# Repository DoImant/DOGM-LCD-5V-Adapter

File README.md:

# 5V Adapter for the DOGMxxxxA Carrier Board.

This board is an adapter with which the 3.3V LCD-DOGMxxxx-A adapter board can also be operated with 5V (e.g. Arduino Nano/Uno).
Because the data flow is only unidirectional to the display, a 74LVC245A octal bus transceiver IC could be used as a level converter.

## Pictures
DOGM 5V to 3.3V Adapter. Front and back side.

Adapter board with LCD display on a breadboard.

Dogm LCD powerconsumption without backlight

Dogm LCD powerconsumtion with 25% backlight

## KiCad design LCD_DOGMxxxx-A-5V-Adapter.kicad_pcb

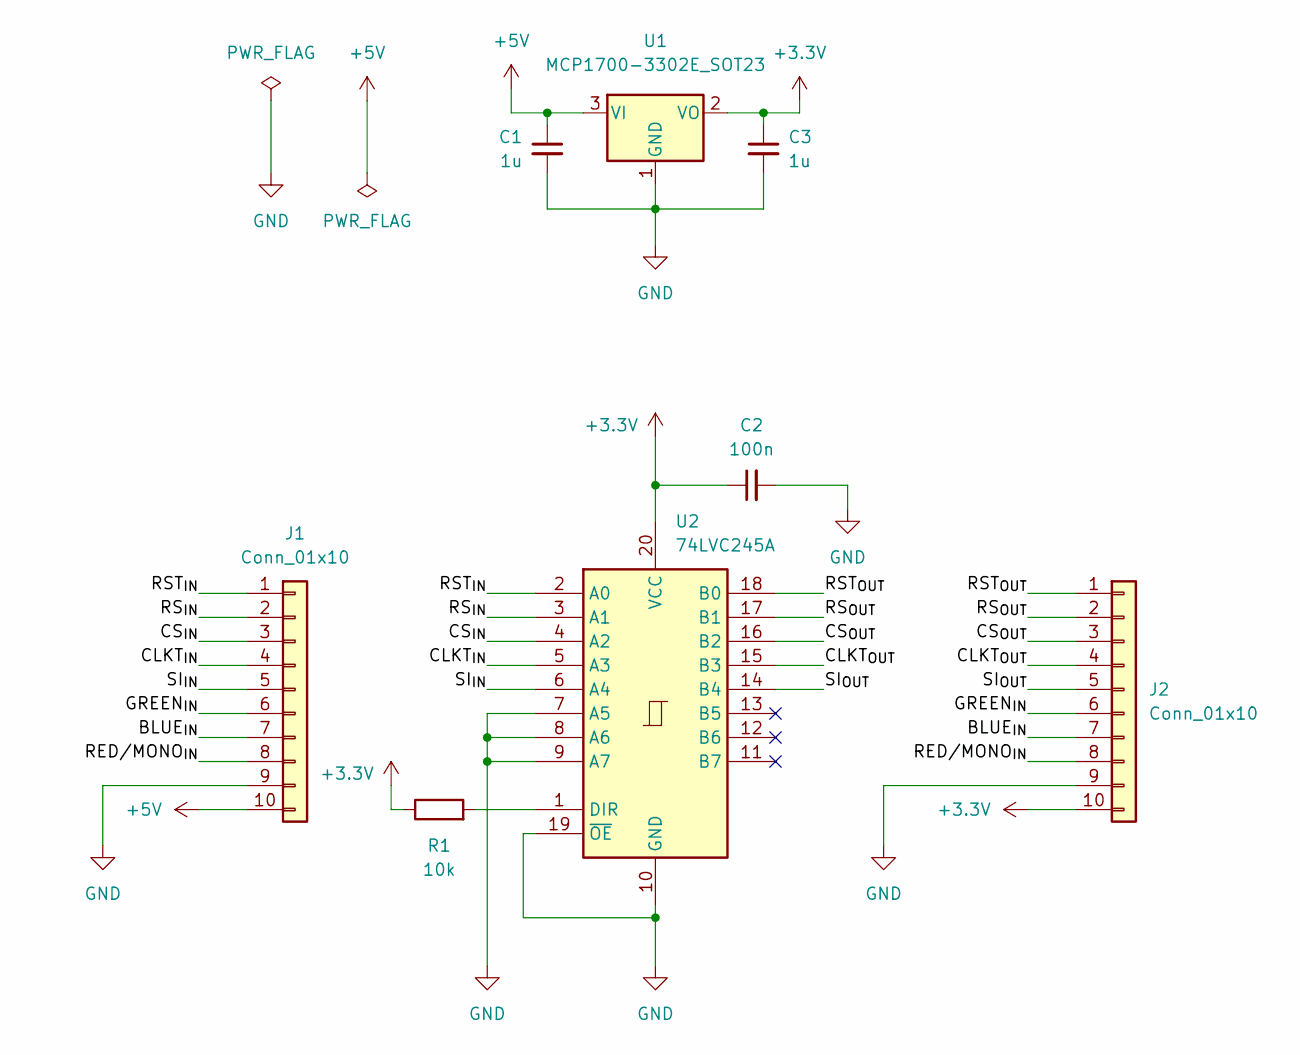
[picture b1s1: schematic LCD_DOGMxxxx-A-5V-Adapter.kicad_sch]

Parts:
C1, C3: 1u; C_1206_3216Metric_Pad1.33x1.80mm_HandSolder
C2: 100n; C_1206_3216Metric_Pad1.33x1.80mm_HandSolder
J1: Conn_01x10; PinHeader_1x10_P2.54mm_Vertical
J2: Conn_01x10; PinSocket_1x10_P2.54mm_Horizontal
R1: 10k; R_1206_3216Metric_Pad1.30x1.75mm_HandSolder
U1: MCP1700-3302E_SOT23; SOT-23
U2: 74LVC245A; TSSOP-20_4.4x6.5mm_P0.65mm

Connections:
+3V3: C2.1, C3.1, J2.10, R1.1, U1.2 (VO), U2.20 (VCC)
+5V: C1.1, J1.10, U1.3 (VI)
/BLUE_{IN}: J1.7, J2.7
/CLKT_{IN}: J1.4, U2.5 (A3)
/CLKT_{OUT}: J2.4, U2.15 (B3)
/CS_{IN}: J1.3, U2.4 (A2)
/CS_{OUT}: J2.3, U2.16 (B2)
/GREEN_{IN}: J1.6, J2.6
/RED/MONO_{IN}: J1.8, J2.8
/RST_{IN}: J1.1, U2.2 (A0)
/RST_{OUT}: J2.1, U2.18 (B0)
/RS_{IN}: J1.2, U2.3 (A1)
/RS_{OUT}: J2.2, U2.17 (B1)
/SI_{IN}: J1.5, U2.6 (A4)
/SI_{OUT}: J2.5, U2.14 (B4)
GND: C1.2, C2.2, C3.2, J1.9, J2.9, U1.1 (GND), U2.7 (A5), U2.8 (A6), U2.9 (A7), U2.10 (GND), U2.19 (~OE)
unnamed: R1.2, U2.1 (DIR)

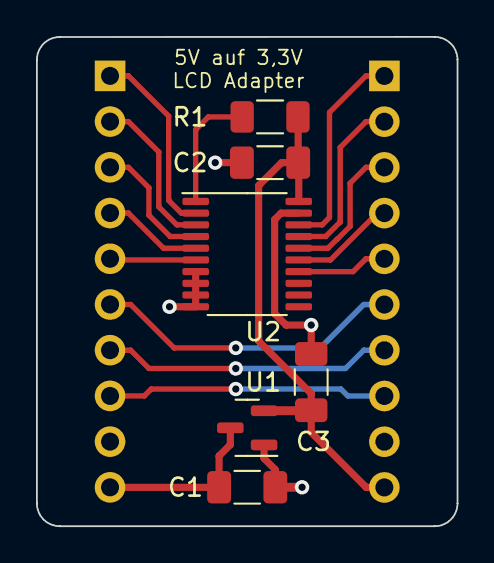
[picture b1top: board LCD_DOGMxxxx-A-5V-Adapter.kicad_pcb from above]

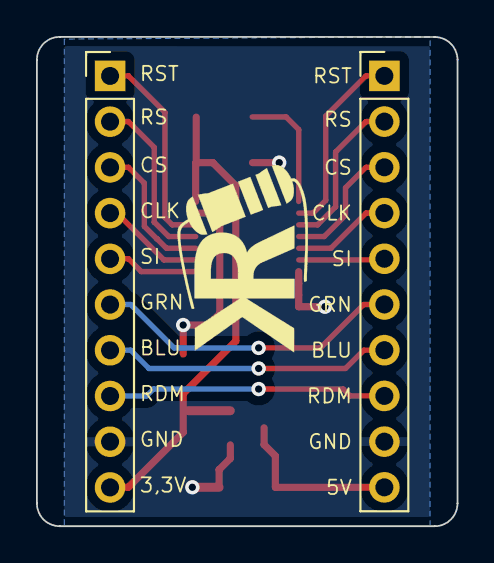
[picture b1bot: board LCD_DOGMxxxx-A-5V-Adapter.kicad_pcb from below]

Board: 2 copper layers, 23.4 x 27.2 mm, 8 parts (2 on the bottom side), 17 nets.

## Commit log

2022-04-18 Corrected incorrect README.md
